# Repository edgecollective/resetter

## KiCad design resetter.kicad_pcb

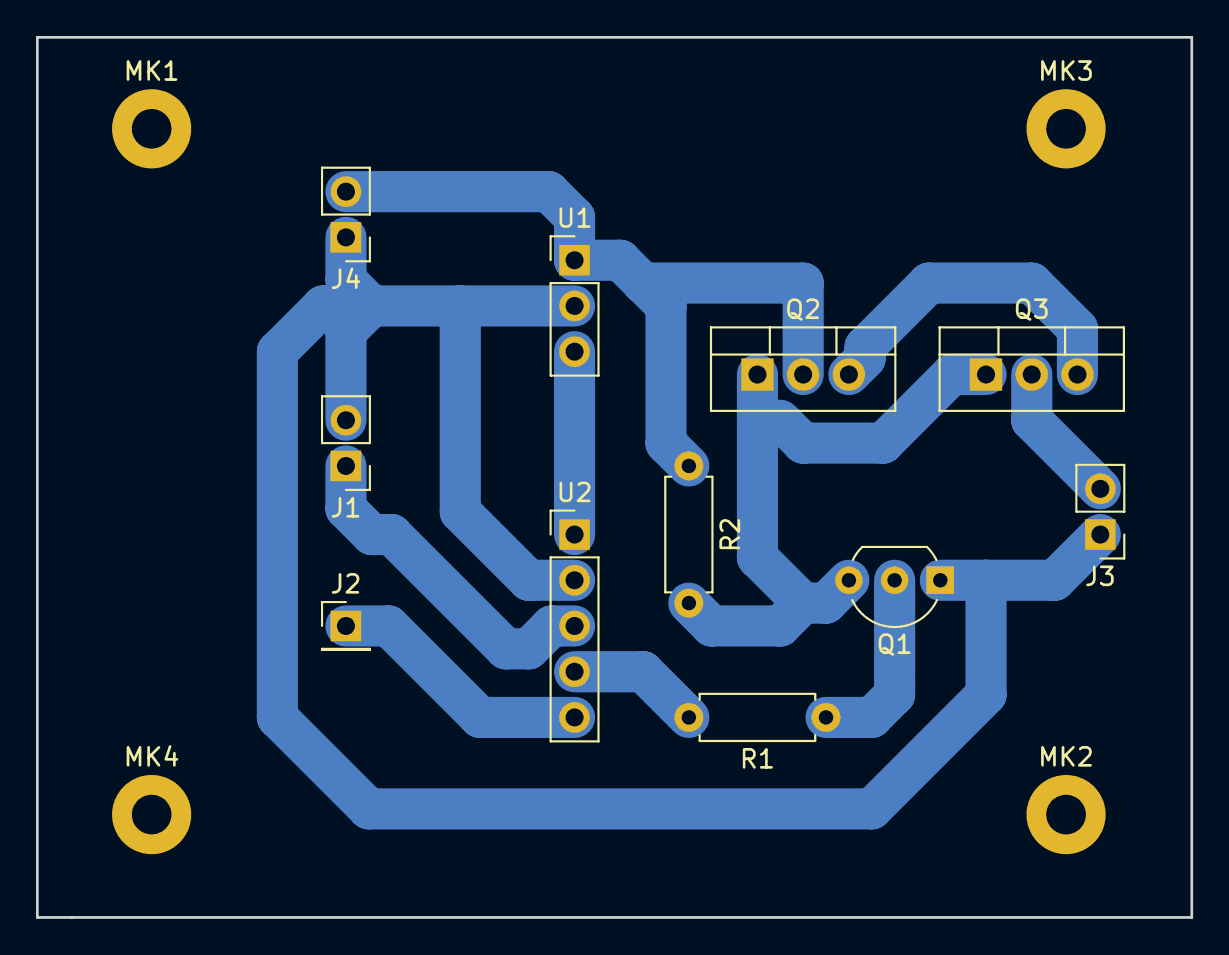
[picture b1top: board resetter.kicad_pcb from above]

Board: 2 copper layers, 64.1 x 48.9 mm, 15 parts (0 on the bottom side), 10 nets.

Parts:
J1: Conn_01x02_Female; Pin_Header_Straight_1x02_Pitch2.54mm
J2: Conn_01x01; Pin_Header_Straight_1x01_Pitch2.54mm
J3, J4: Conn_01x02; Pin_Header_Straight_1x02_Pitch2.54mm
MK1, MK2, MK3, MK4: Mounting_Hole; MountingHole_2.2mm_M2_Pad
Q1: 2N3904-AP; TO-92_Inline_Wide
Q2, Q3: Q_PMOS_GDS; TO-220-3_Vertical
R1, R2: R; R_Axial_DIN0207_L6.3mm_D2.5mm_P7.62mm_Horizontal
U1: VX7805; Pin_Header_Straight_1x03_Pitch2.54mm
U2: adafruit_tpl5110; Pin_Header_Straight_1x05_Pitch2.54mm

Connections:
GND: J1.2, J3.1, J4.1, Q1.1, U1.2, U2.2
unnamed: J1.1, U2.3
unnamed: J2.1, U2.5
unnamed: J3.2, Q3.2
unnamed: J4.2, Q2.2, R2.1, U1.1
unnamed: Q1.2, R1.1
unnamed: Q1.3, Q2.1, Q3.1, R2.2
unnamed: Q2.3, Q3.3
unnamed: R1.2, U2.4
unnamed: U1.3, U2.1
